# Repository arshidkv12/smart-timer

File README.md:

# Smart Timer Switch Using ESP8266 and RTC

A simple **Wi-Fi programmable timer switch** based on **ESP8266 and RTC**. It can automatically turn a connected device ON and OFF according to a configured schedule.

No internet connection is required. The timer creates its own local Wi-Fi network for configuration.

## Features

* 📡 ESP8266-based local Wi-Fi configuration
* ⏰ Real-time clock (RTC) for accurate timekeeping
* 🔌 5V relay for controlling electrical loads
* 🌐 Simple web-based configuration
* 🚫 No internet required
* 💾 Stores configuration locally
* 🔘 Physical button to enable configuration mode
* 📱 Configure using a mobile phone or computer

## Project Images

### Prototype

### Circuit Diagram

### Web Configuration

## YouTube

📺 **Watch the project demo:**  
▶️ [Watch the Smart Timer Switch Demo on YouTube](https://youtube.com/shorts/wJGOkK_HlXM)

## Main Blocks

The project mainly consists of four blocks:

1. **ESP8266** – Wi-Fi and controller
2. **5V Relay** – Controls the connected load
3. **Real-Time Clock (RTC)** – Keeps track of time
4. **Voltage Regulator** – Provides the required regulated voltage

## How It Works

1. Power on the timer switch.
2. Press and hold the configuration button.
3. The ESP8266 enables local Wi-Fi mode.
4. Connect your phone or computer to the timer's Wi-Fi network.
5. Open a browser and go to:

```text
192.168.1.1
```

6. Set the current time if required.
7. Configure the ON and OFF schedule.
8. The timer automatically controls the connected load according to the schedule.

## Hardware

* ESP8266
* DS1302 RTC
* 5V Relay Module
* AMS1117-3.3V Voltage Regulator
* Push Button
* Resistors and capacitors
* Power supply
* Connected load

## Configuration

The timer uses a local web interface, so you don't need a cloud service or internet connection.

Connect to the timer's Wi-Fi, open `192.168.1.1` in your browser, and configure the required schedule.

## Example

For example:

```text
ON  → 08:01 PM
OFF → 08:03 PM
```

The relay will automatically switch the connected load according to the configured schedule.

## Advantages

* Simple configuration
* No internet dependency
* No LCD or LED display required
* Easy to modify the schedule
* Low-cost hardware
* Useful for automatic switching applications

## Project Structure

```text
├── firmware/
├── img/
│   ├── block-diagram.png
│   ├── diagram.png
│   ├── img.png
│   └── pcb.png
├── PCB/
├── README.md
└── project-report.pages
```

## License

This project is open source. See the `LICENSE` file for details.

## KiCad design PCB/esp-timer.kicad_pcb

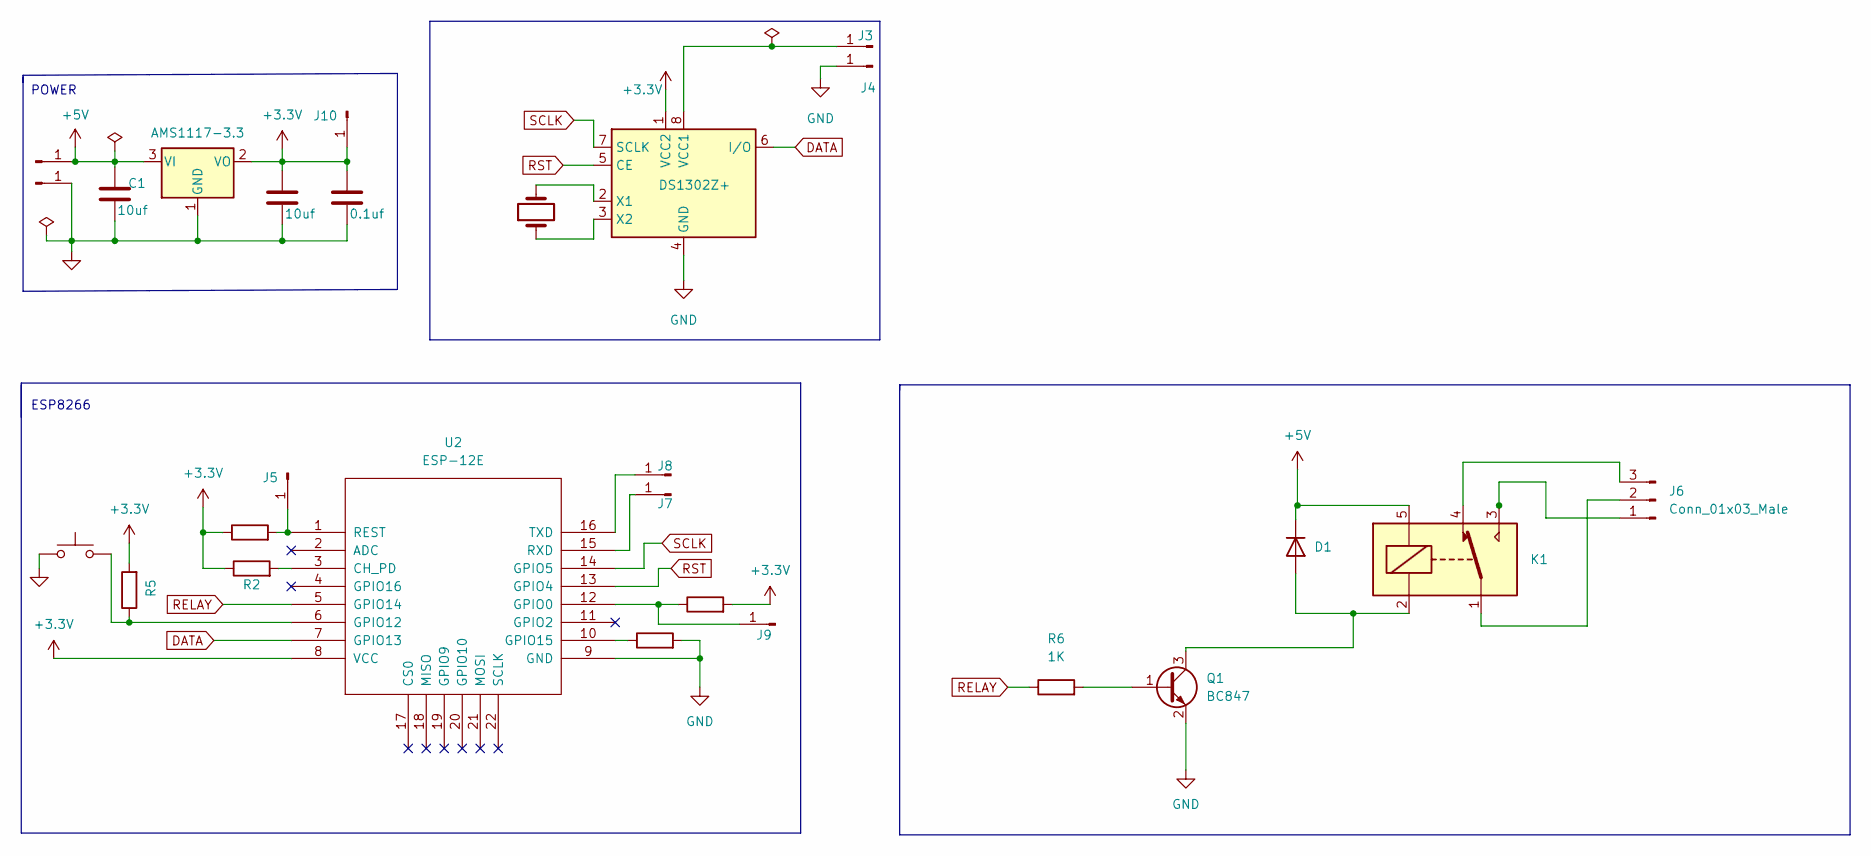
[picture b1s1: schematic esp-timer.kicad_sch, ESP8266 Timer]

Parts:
C1, C2: 10uf; C_1206_3216Metric_Pad1.33x1.80mm_HandSolder
C3: 0.1uf; C_1206_3216Metric_Pad1.33x1.80mm_HandSolder
D1: 1N4007; D_MiniMELF
J1, J2, J3, J4, J5, J7, J8, J9, J10: Conn_01x01_Male; SolderWirePad_1x01_SMD_1x2mm
J6: Conn_01x03_Male; TerminalBlock_Phoenix_MKDS-1,5-3_1x03_P5.00mm_Horizontal
K1: SANYOU_SRD_Form_C; Relay_SPDT_SANYOU_SRD_Series_Form_C
Q1: BC847; SOT-23
R1, R2, R3, R4, R5: R; R_1206_3216Metric_Pad1.30x1.75mm_HandSolder
R6: 1K; R_1206_3216Metric
SW1: SW_Push; SW_PUSH_6mm_H13mm
U1: AMS1117-3.3; SOT-223-3_TabPin2
U2: ESP-12E; ESP-12E_SMD
U3: DS1302Z+; SOIC-8_3.9x4.9mm_P1.27mm
Y1: Crystal; Crystal_SMD_G8-2Pin_3.2x1.5mm

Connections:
+3V3: C2.1, C3.1, J10.1, R1.1, R2.1, R4.2, R5.2, U1.2 (VO), U2.8 (VCC), U3.1 (VCC2)
+5V: C1.1, D1.1 (K), J1.1, K1.5, U1.3 (VI)
DATA: U2.7 (GPIO13), U3.6 (I/O)
GND: C1.2, C2.2, C3.2, J2.1, J4.1, Q1.2 (E), R3.2, SW1.1, U1.1 (GND), U2.9 (GND), U3.4 (GND)
unnamed: D1.2 (A), K1.2, Q1.3 (C)
unnamed: J3.1, U3.8 (VCC1)
unnamed: J6.1, K1.3
unnamed: J6.2, K1.1
unnamed: J6.3, K1.4
unnamed: Q1.1 (B), R6.2
unnamed: J5.1, R1.2, U2.1 (REST)
unnamed: R2.2, U2.3 (CH_PD)
unnamed: R3.1, U2.10 (GPIO15)
unnamed: J9.1, R4.1, U2.12 (GPIO0)
unnamed: R5.1, SW1.2, U2.6 (GPIO12)
unnamed: J7.1, U2.15 (RXD)
unnamed: J8.1, U2.16 (TXD)
unnamed: U3.3 (X2), Y1.1
unnamed: U3.2 (X1), Y1.2
RELAY: R6.1, U2.5 (GPIO14)
RST: U2.13 (GPIO4), U3.5 (CE)
SCLK: U2.14 (GPIO5), U3.7 (SCLK)

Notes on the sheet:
POWER
ESP8266

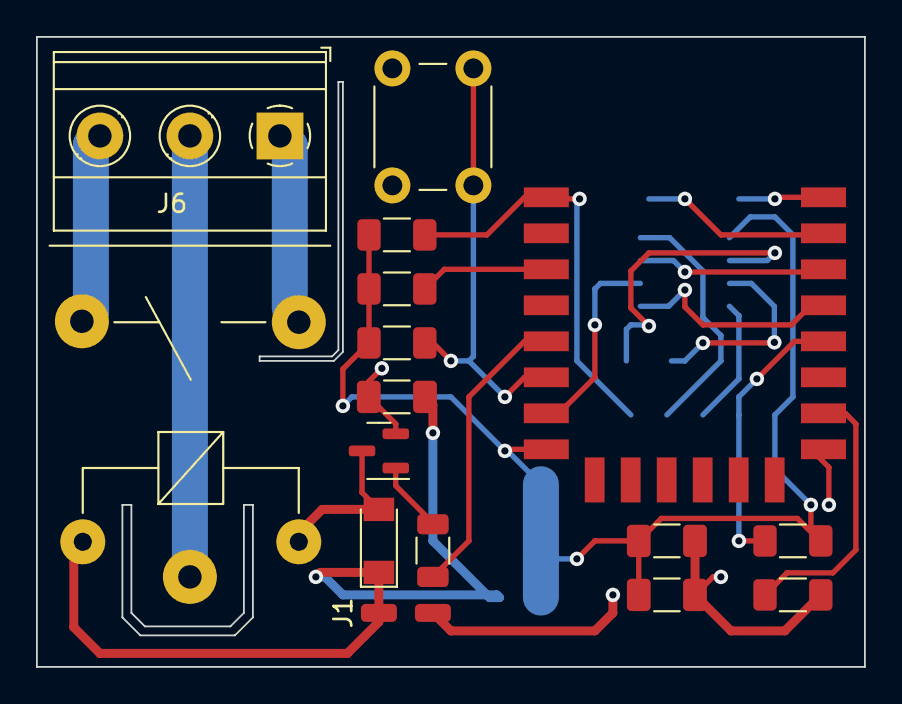
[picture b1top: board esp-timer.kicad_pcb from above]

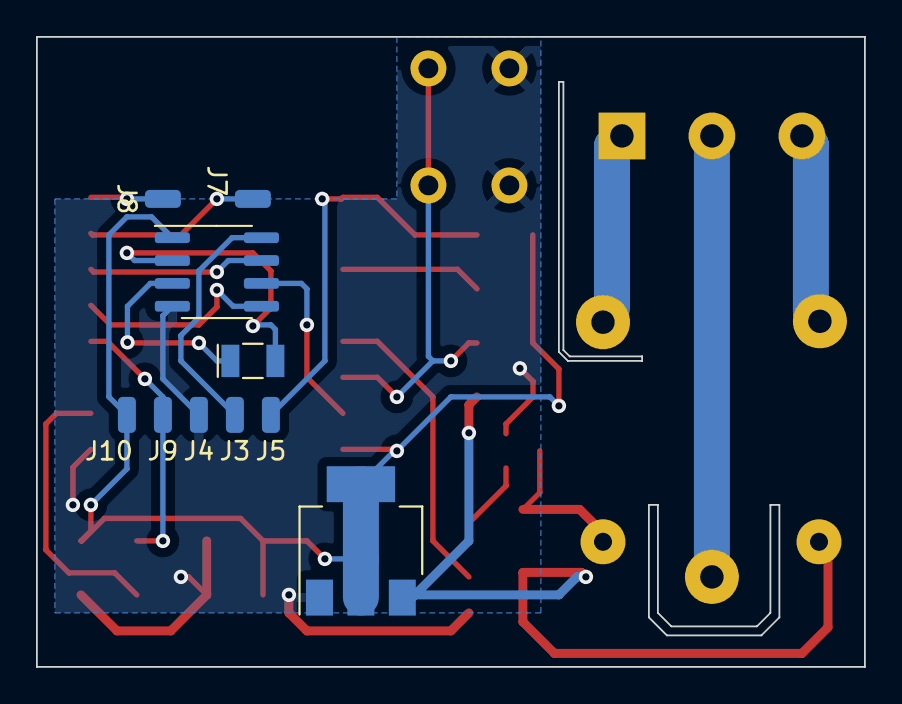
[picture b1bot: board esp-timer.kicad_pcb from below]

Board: 2 copper layers, 46.0 x 35.0 mm, 27 parts (10 on the bottom side), 22 nets.
